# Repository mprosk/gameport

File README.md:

# GamePort to CV
KOSMO format module that converts a GamePort joystick to gate and control voltages

The X and Y movement of the stick is output as two independent control voltages ranging from 0V to +5V. The two buttons are output as gate signals, also from 0V to +5V

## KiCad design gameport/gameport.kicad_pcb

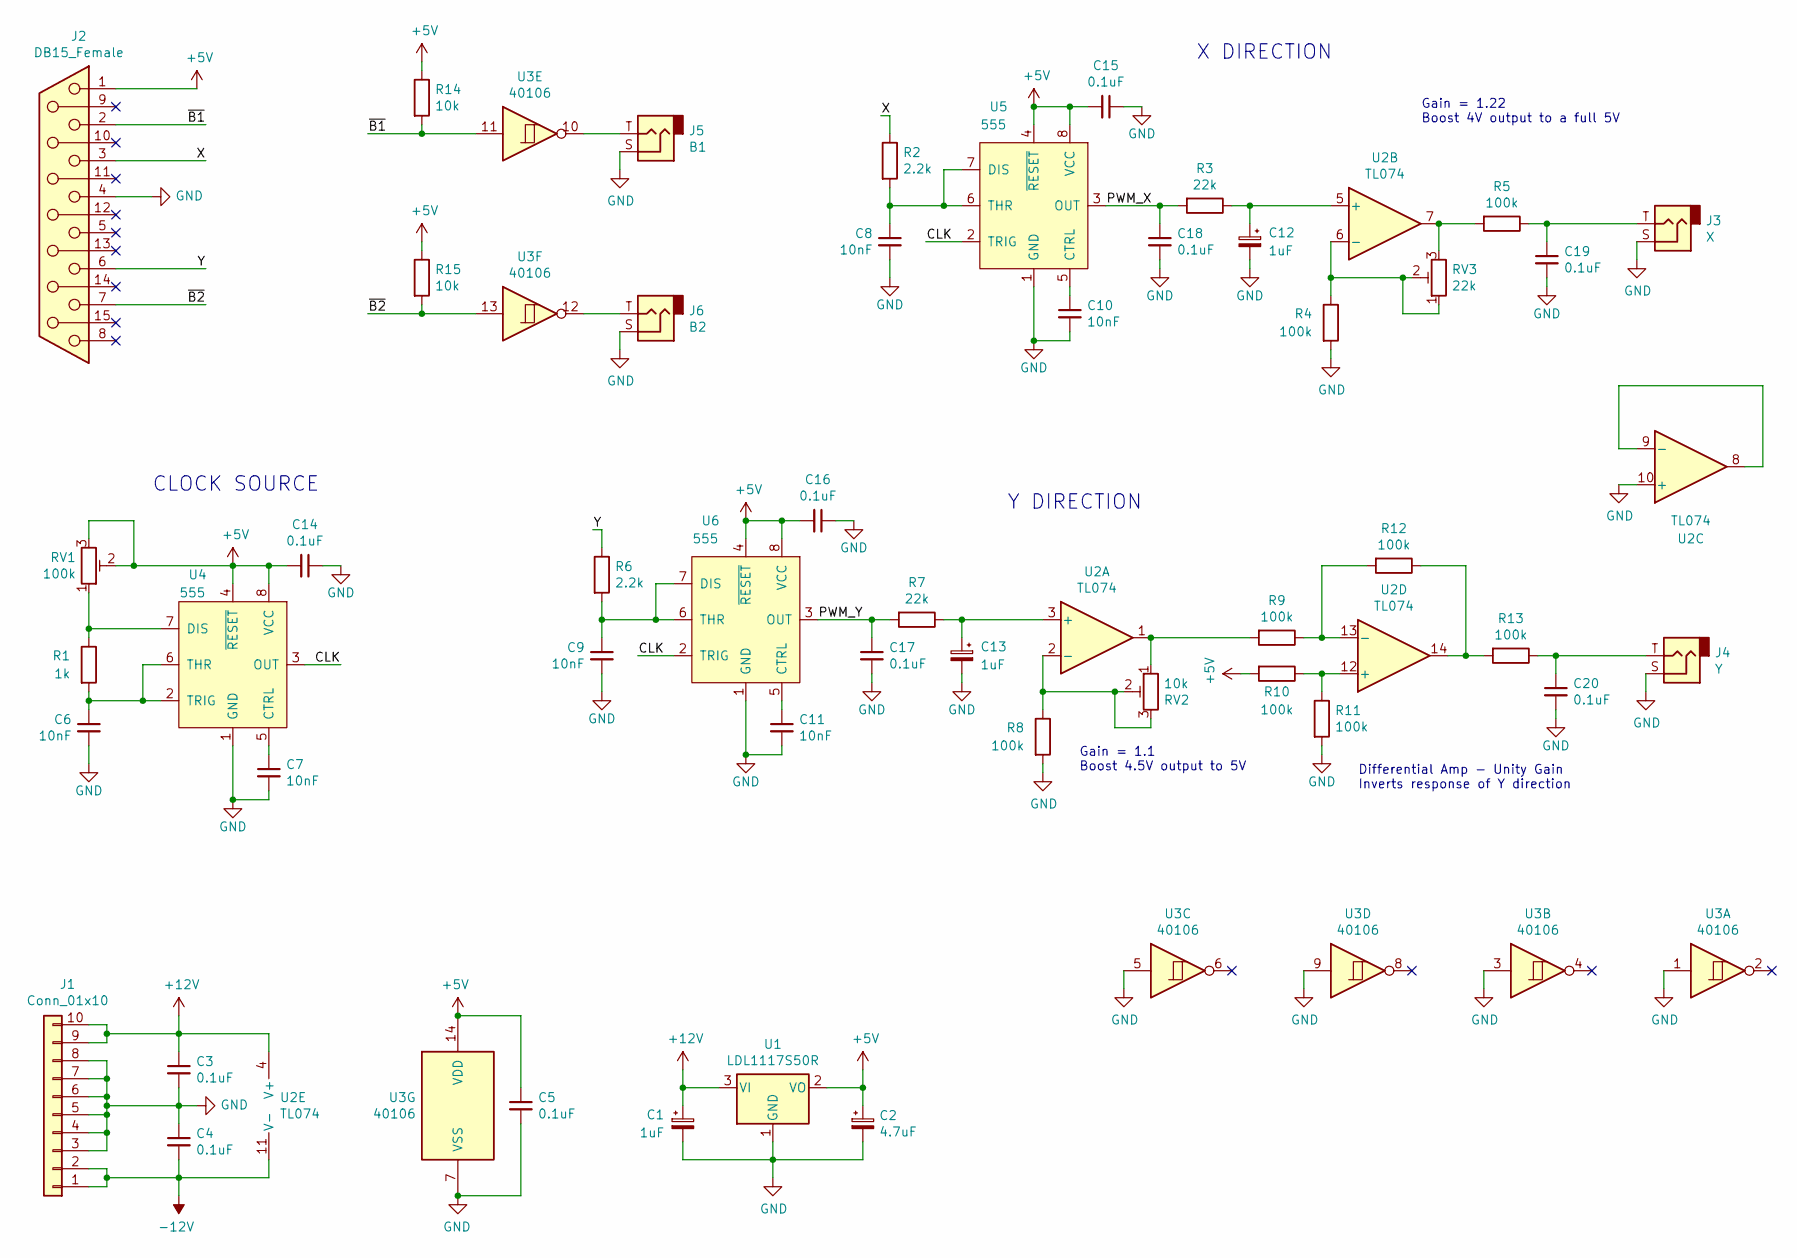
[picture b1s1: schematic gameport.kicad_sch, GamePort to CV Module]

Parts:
C1, C12, C13: 1uF; CP_Radial_D5.0mm_P2.00mm
C2: 4.7uF; CP_Radial_D5.0mm_P2.00mm
C3, C4, C5, C14, C15, C16, C17, C18, C19, C20: 0.1uF; C_Disc_D3.0mm_W1.6mm_P2.50mm
C6, C7, C8, C9, C10, C11: 10nF; C_Disc_D3.0mm_W1.6mm_P2.50mm
J1: Conn_01x10; IDC-Header_2x05_P2.54mm_Vertical
J2: DB15_Female; DSUB-15_Female_Horizontal_P2.77x2.84mm_EdgePinOffset4.94mm_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
J3: X; Molex_KK-254_AE-6410-02A_1x02_P2.54mm_Vertical
J4: Y; Molex_KK-254_AE-6410-02A_1x02_P2.54mm_Vertical
J5: B1; Molex_KK-254_AE-6410-02A_1x02_P2.54mm_Vertical
J6: B2; Molex_KK-254_AE-6410-02A_1x02_P2.54mm_Vertical
R1: 1k; R_Axial_DIN0207_L6.3mm_D2.5mm_P10.16mm_Horizontal
R2, R6: 2.2k; R_Axial_DIN0207_L6.3mm_D2.5mm_P10.16mm_Horizontal
R3, R7: 22k; R_Axial_DIN0207_L6.3mm_D2.5mm_P10.16mm_Horizontal
R4, R5, R8, R9, R10, R11, R12, R13: 100k; R_Axial_DIN0207_L6.3mm_D2.5mm_P10.16mm_Horizontal
R14, R15: 10k; R_Axial_DIN0207_L6.3mm_D2.5mm_P10.16mm_Horizontal
RV1: 100k; Potentiometer_Bourns_3296Y_Vertical
RV2: 10k; Potentiometer_Bourns_3296Y_Vertical
RV3: 22k; Potentiometer_Bourns_3296Y_Vertical
U1: LDL1117S50R; SOT-223-3_TabPin2
U2: TL074; DIP-14_W7.62mm
U3: 40106; DIP-14_W7.62mm
U4, U5, U6: 555; DIP-8_W7.62mm

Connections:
+5V: C2.1, C5.1, C14.2, C15.2, C16.2, J2.1, R10.2, R14.1, R15.1, RV1.2, RV1.3, U1.2 (VO), U3.14 (VDD), U4.4 (~RESET), U4.8 (VCC), U5.4 (~RESET), U5.8 (VCC), U6.4 (~RESET), U6.8 (VCC)
+12V: C1.1, C3.1, J1.9, J1.10, U1.3 (VI), U2.4 (V+)
-12V: C4.2, J1.1, J1.2, U2.11 (V-)
/CLK: U4.3 (OUT), U5.2 (TRIG), U6.2 (TRIG)
/PWM_X: C18.1, R3.2, U5.3 (OUT)
/PWM_Y: C17.1, R7.2, U6.3 (OUT)
/X: J2.3, R2.1
/Y: J2.6, R6.1
/~B1: J2.2, R14.2, U3.11
/~B2: J2.7, R15.2, U3.13
GND: C1.2, C2.2, C3.2, C4.1, C5.2, C6.2, C7.2, C8.2, C9.2, C10.2, C11.2, C12.2, C13.2, C14.1, C15.1, C16.1, C17.2, C18.2, C19.2, C20.2, J1.3, J1.4, J1.5, J1.6, J1.7, J1.8, J2.4, J3.S, J4.S, J5.S, J6.S, R4.2, R8.2, R11.2, U1.1 (GND), U2.10 (+), U3.1, U3.3, U3.5, U3.7 (VSS), U3.9, U4.1 (GND), U5.1 (GND), U6.1 (GND)
unnamed: C6.1, R1.2, U4.2 (TRIG), U4.6 (THR)
unnamed: C7.1, U4.5 (CTRL)
unnamed: C8.1, R2.2, U5.6 (THR), U5.7 (DIS)
unnamed: C9.1, R6.2, U6.6 (THR), U6.7 (DIS)
unnamed: C10.1, U5.5 (CTRL)
unnamed: C11.1, U6.5 (CTRL)
unnamed: C12.1, R3.1, U2.5 (+)
unnamed: C13.1, R7.1, U2.3 (+)
unnamed: C19.1, J3.T, R5.1
unnamed: C20.1, J4.T, R13.1
unnamed: J5.T, U3.10
unnamed: J6.T, U3.12
unnamed: R1.1, RV1.1, U4.7 (DIS)
unnamed: R4.1, RV3.1, RV3.2, U2.6 (-)
unnamed: R5.2, RV3.3, U2.7
unnamed: R8.1, RV2.2, RV2.3, U2.2 (-)
unnamed: R9.2, RV2.1, U2.1
unnamed: R10.1, R11.1, U2.12 (+)
unnamed: R12.1, R13.2, U2.14
unnamed: R9.1, R12.2, U2.13 (-)
unnamed: U2.8, U2.9 (-)

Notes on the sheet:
CLOCK SOURCE
Gain = 1.22 Boost 4V output to a full 5V
Y DIRECTION
X DIRECTION
Gain = 1.1 Boost 4.5V output to 5V
Differential Amp - Unity Gain Inverts response of Y direction

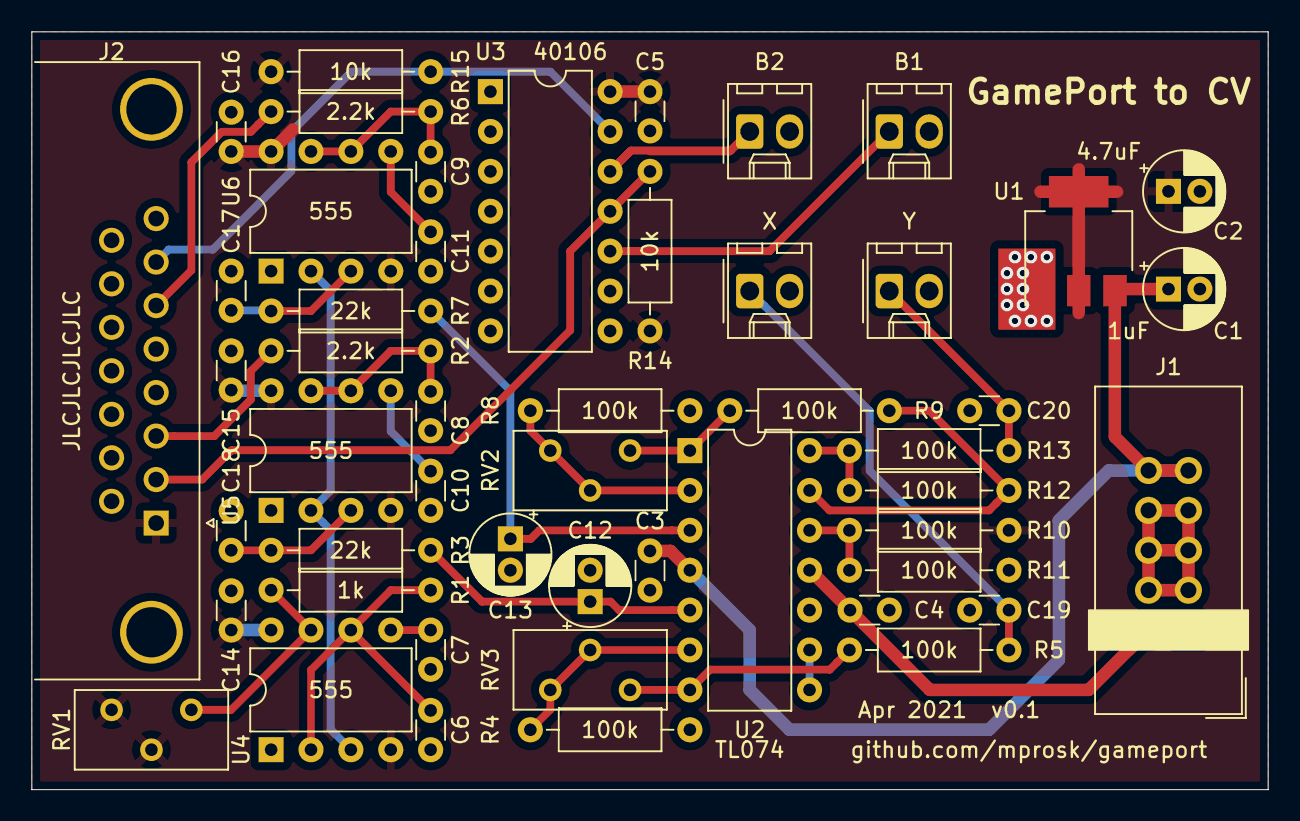
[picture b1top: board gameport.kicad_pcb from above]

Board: 2 copper layers, 78.7 x 48.3 mm, 50 parts (0 on the bottom side), 32 nets.

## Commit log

2021-04-05 add files from other repo
2021-04-05 cleanup
2021-04-07 Add LTSpice sim of diff amp
2021-04-07 Update schematic
2021-04-07 Complete layout
2021-04-08 Complete faceplate
2021-04-22 Update faceplate
2022-04-15 Update to Kicad6. Use kosmo-lib submodule
2022-04-18 local changes
